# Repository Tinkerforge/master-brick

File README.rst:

Master Brick
============

This repository contains the firmware source code and the hardware design
files. The documentation generator configs can be found at
https://github.com/Tinkerforge/generators

Repository Content
------------------

software/:
 * examples/: Examples for all supported languages
 * build/: Compiled files
 * src/: Source code of firmware
 * Makefile: Makefile to build project

hardware/:
 * Contains KiCad project files and additionally schematics as PDF

datasheets/:
 * Contains datasheets for sensors and complex ICs that are used

Hardware
--------

The hardware is designed with the open source EDA Suite KiCad
(http://www.kicad.org). Before you are able to open the files,
you have to install the Tinkerforge kicad-libraries
(https://github.com/Tinkerforge/kicad-libraries). You can either clone
them directly in hardware/ or clone them in a separate folder and
symlink them into hardware/
(ln -s kicad_path/kicad-libraries project_path/hardware). After that you
can open the .pro file in hardware/ with KiCad and from there view and
modify the schematics and the PCB layout.

Software
--------

If you want to do your own Brick/Bricklet firmware development we highly
recommend that you use our build environment setup script and read the
tutorial (https://www.tinkerforge.com/en/doc/Tutorials/Tutorial_Build_Environment/Tutorial.html).

To compile the C code we recommend you to install the newest GNU Arm Embedded
Toolchain (https://launchpad.net/gcc-arm-embedded/+download).
You also need to install bricklib (https://github.com/Tinkerforge/bricklib).

You can either clone it directly in software/src/ or clone it in a
separate folder and symlink it into software/src/
(ln -s bricklib_path/bricklib project_path/software/src/). Finally make sure to
have CMake installed (http://www.cmake.org/cmake/resources/software.html).

After that you can build the firmware by invoking make in software/.
The firmware (.bin) can then be found in software/build/ and uploaded
with brickv (click button "Flashing" on start screen).

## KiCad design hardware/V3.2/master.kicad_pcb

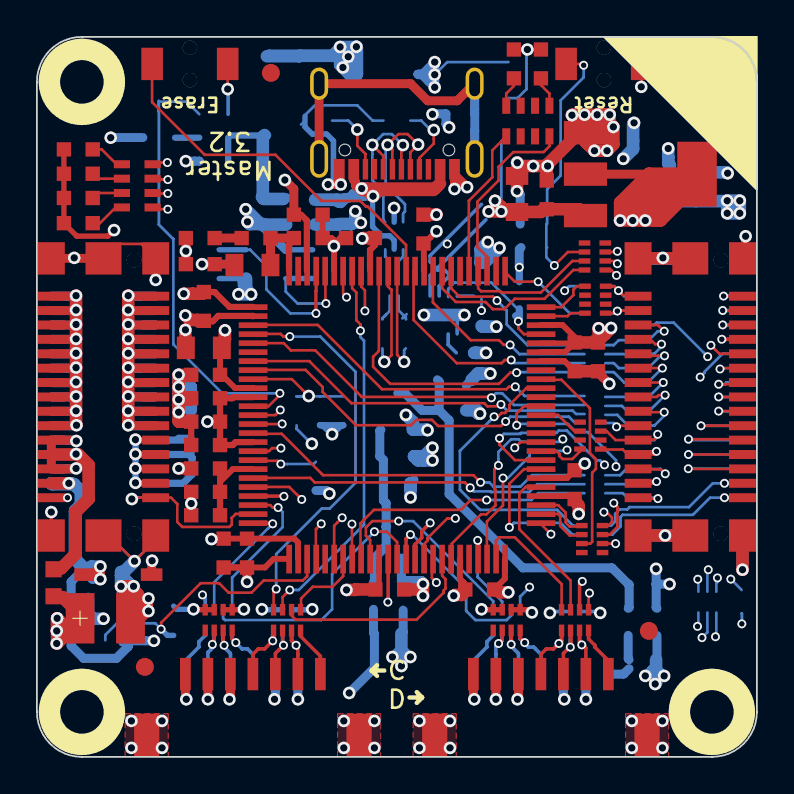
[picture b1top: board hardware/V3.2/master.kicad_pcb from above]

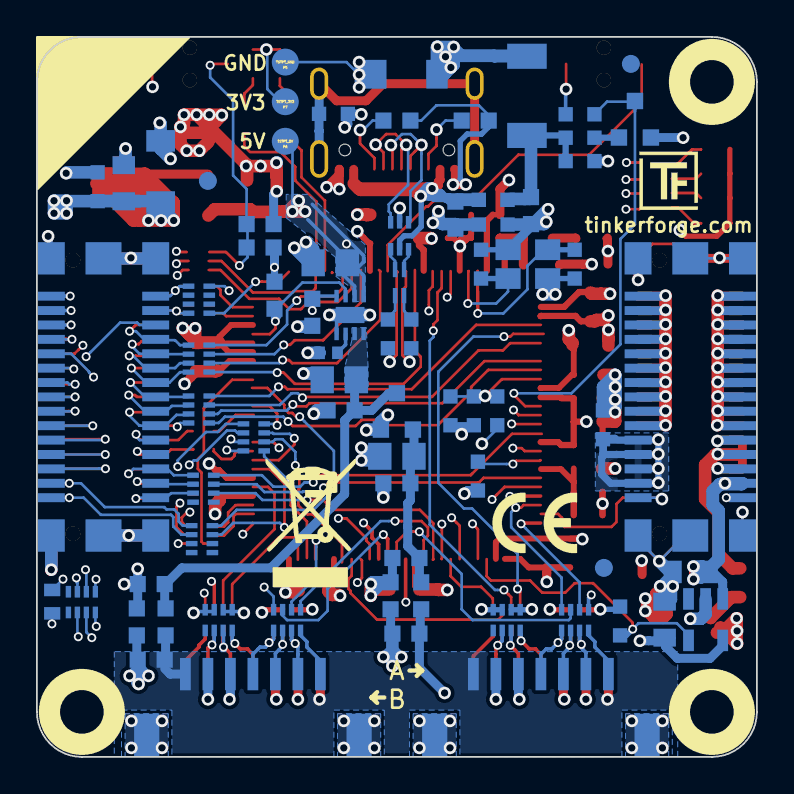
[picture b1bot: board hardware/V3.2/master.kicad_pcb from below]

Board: 4 copper layers, 40.0 x 40.0 mm, 137 parts (76 on the bottom side), 151 nets.

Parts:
C10, C11, C12, C13: DNP; C0603
C14, C46, C47: 1uF; C0603F
C15, C21, C29, C35, C39: 10µF/10V; C0805
C16, C20, C22, C23, C24, C25, C26, C28, C30, C31, C32, C33, C34, C37, C38, C401: 100nF; C0603
C17: 100µF; 3528-21
C18, C19, C36: 4.7µF; C0603
C27: 2.2µF; C0603
C40: DNP; C0402F
C41, C43, C45: 10uF; C0805E
C42, C44: 100nF; C0603F
C48, C49, C50, C51: 2.2uF; C0603F
C101: 4.7nF; C0603F
CP1, CP2, CP3, CP4: 220pF; 4X0402
D1, D3, D4, D5, D6: blue; D0603
D2: red; D0603
D11: PMEG4050; SOD-128
D12: Z5V; MiniMelf
D13: Z3.3V; MiniMelf
D14: B0520LW; SOD-123
FB1, FB3, FB101, FB102: FB; C0603
FB4: FB; R0603F
Fiducial_Mark: VAL**; Fiducial_Mark
Fiducial_Mark#2, Fiducial_Mark#3, Fiducial_Mark#4, Fiducial_Mark#5, Fiducial_Mark#6: VAL**; Fiducial_Mark
J1: USB-C; USB-C-2
J2, J3, J4, J5: DRILL; DRILL_NP
J6: STACK-UP-HIGH; BTB08-ACS-TOP
J7: STACK-HIGH; BTB08-ACS-BTM
J8: STACK-UP-LOW; BTB08-ACS-TOP
J9: STACK-DOWN; BTB08-ACS-BTM
L1: 744230900; WE-CNSW-0603
L2: LBR2012T100K; C0805
L3, L4, L5, L6: FB; R0603F
P1: Port A; CON-SENSOR2
P2: Port B; CON-SENSOR2
P3: Port C; CON-SENSOR2
P4: Port D; CON-SENSOR2
P5: TSTPT_GND; TSTPT
P6: TSTPT_5V; TSTPT
P7: TSTPT_3V3; TSTPT
Q1: 2N7002P; SOT23GDS
R3, R4: 27; R0603
R5, R18: 5k1; R0603F
R6: 47k; R0603
R7: 1k; R0603F
R8, R11, R17: 10k; R0603
R9, R10, R12, R13: DNP; R0603
R15: 100k; R0603
R16: 1R0; R0603
R101: 100k; R0603F
R301: 82; R0402E
RP3, RP4: 1k; 0603X4
RP5, RP6, RP7, RP9, RP301, RP302, RP303, RP304, RP305, RP306, RP307, RP308, RP310: 82; 4X0402
RP8, RP309: 1k; 4X0402
SW1: Reset; TACT-SWITCH
SW2: Erase; TACT-SWITCH
U1: SAM4S4CA; LQFP100
U2: 82400152; SOT563-SPEC
U3: TPS22975; WSON8-2x2
U4: AP7333-33SRG; SOT23-3
U12: LD1117; SOT-223
U13: STMPS2171STR; SOT23-5L
VAL: WEEE_7mm
VAL#2: CE_5mm
X1: 16Mhz; CRYSTAL_3225

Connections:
3,3VBricklet: C51.2, L4.1, P1.3, P2.3, P3.3, P4.3
3V3: C15.1, C16.1, C18.1, C19.1, C20.1, C22.1, C24.1, C25.1, C26.1, C29.1, C31.1, C35.1, C38.1, D1.1 (A), D2.1 (A), D3.1 (A), D4.1 (A), D5.1 (A), D6.1 (A), D13.2 (K), D14.1 (A), P7.1, R7.1, R9.2, R11.1, R12.2, R101.2, SW2.2, U1.1 (ADVREF), U1.10 (VDDIN), U1.27 (VDDIO), U1.50 (VDDIO), U1.69 (VDDIO), U1.91 (VDDIO), U1.98 (VDDIO), U12.2 (VOUT), U13.5 (IN)
3V3-EN: R17.1, U1.28 (PA16/PGMD4), U13.4 (EN)
5VBricklet: C48.2, L3.2, P1.1, P2.1, P3.1, P4.1
Bricklet_Enable: R7.2, U1.72 (PA1/PGMEN1), U3.3 (ON)
GND: C10.2, C11.2, C12.2, C13.2, C14.2, C15.2, C16.2, C17.2, C18.2, C19.2, C20.2, C21.2, C22.2, C23.2, C24.2, C25.2, C26.2, C27.2, C28.2, C29.2, C30.2, C31.2, C32.2, C33.2, C34.2, C35.2, C36.2, C37.2, C38.2, C39.2, C40.2, C41.1, C42.1, C43.1, C44.1, C45.1, C46.1, C49.1, C50.1, C101.1, C401.2, CP1.5 (R4), CP1.6 (R3), CP1.7 (R2), CP1.8 (R1), CP2.5 (R4), CP2.6 (R3), CP2.7 (R2), CP2.8 (R1), CP3.5 (R4), CP3.6 (R3), CP3.7 (R2), CP3.8 (R1), CP4.5 (R4), CP4.6 (R3), CP4.7 (R2), CP4.8 (R1), D12.1 (A), D13.1 (A), FB3.2, FB101.1, FB102.2, J6.EP, J7.EP, J8.EP, J9.EP, L5.1, L6.2, P5.1, Q1.S, R6.1, R10.1, R13.1, R15.1, R17.2, SW1.2, U1.2 (GND), U1.22 (PA23), U1.26 (GND), U1.45 (GND), U1.54 (PC28), U1.70 (GND), U1.71 (PC14), U1.73 (PC16), U1.95 (GND), U3.5 (GND), U3.EXP, U4.1 (GND), U12.1 (GND), U13.2 (GND), X1.3
GNDD1: C48.1, C51.1, L5.2, L6.1, P1.2, P1.EP, P2.2, P2.EP, P3.2, P3.EP, P4.2, P4.EP
LED1: RP4.1, U1.92 (PC24)
LED2: RP4.2, U1.94 (PC25)
LED3: RP4.3, U1.13 (PC26)
LED4: RP4.4, U1.17 (PC27)
unnamed: C10.1, R9.1, R10.2, U1.9 (PB3/AD7)
unnamed: C11.1, R12.1, R13.2, U1.19 (PC15/AD11)
unnamed: C27.1, C28.1, C30.1, C32.1, C33.1, C34.1, C401.1, L2.1, U1.11 (VDDOUT), U1.16 (VDDCORE), U1.36 (VDDCORE), U1.56 (VDDCORE), U1.85 (VDDCORE)
unnamed: C36.1, R16.1
unnamed: C37.1, L2.2, R16.2, U1.100 (VDDPLL)
unnamed: C40.1, U3.6 (CT)
unnamed: C41.2, C42.2, C49.2, L3.1, U3.7 (VOUT), U3.8 (VOUT), U4.3 (VIN)
unnamed: C43.2, C44.2, C50.2, L4.2, U4.2 (VOUT)
unnamed: C47.2, FB1.2, J1.1 (5V), U2.5 (VDD)
unnamed: CP1.2, P1.6, RP5.7 (R2)
unnamed: CP1.3, P1.5, RP5.6 (R3)
unnamed: CP1.4, P1.4, RP5.5 (R4)
unnamed: CP2.2, P2.6, RP6.7 (R2)
unnamed: CP2.3, P2.5, RP6.6 (R3)
unnamed: CP2.4, P2.4, RP6.5 (R4)
unnamed: CP3.2, P3.6, RP7.7 (R2)
unnamed: CP3.3, P3.5, RP7.6 (R3)
unnamed: CP3.4, P3.4, RP7.5 (R4)
unnamed: CP4.2, P4.6, RP9.7 (R2)
unnamed: CP4.3, P4.5, RP9.6 (R3)
unnamed: CP4.4, P4.4, RP9.5 (R4)
unnamed: D1.2 (K), RP3.1
unnamed: D2.2 (K), RP3.4
unnamed: D3.2 (K), RP4.8 (R1)
unnamed: D4.2 (K), RP4.7 (R2)
unnamed: D5.2 (K), RP4.6 (R3)
unnamed: D6.2 (K), RP4.5 (R4)
unnamed: FB4.1, J8.22 (5V), J8.24 (5V), J8.26 (5V), J9.22 (5V), J9.24 (5V), J9.26 (5V)
unnamed: FB102.1, J1.SHD
unnamed: J1.2 (D-), U2.3 (IO2)
unnamed: J1.3 (D+), U2.1 (IO1)
unnamed: J1.4 (CC1), R5.1
unnamed: J1.5 (CC2), R18.1
unnamed: J6.1 (SPI-MISO), J7.1 (SPI-MISO), RP305.7 (R2)
unnamed: J6.2 (I2C-SDA/TDI), J7.2 (I2C-SDA/TDI), RP8.4, RP310.1
unnamed: J6.3 (SPI-MOSI), J7.3 (SPI-MOSI), RP305.6 (R3)
unnamed: J6.4 (I2C-SCL/TDO), J7.4 (I2C-SCL/TDO), RP8.1, RP310.4
unnamed: J6.5 (SPI-SCLK), J7.5 (SPI-SCLK), RP305.5 (R4)
unnamed: J6.6 (SEL-00), J7.8 (SEL-01), RP301.1
unnamed: J6.7 (RESET), J7.7 (RESET), RP309.7 (R2)
unnamed: J6.8 (SEL-01), J7.10 (SEL-02), RP301.2
unnamed: J6.9 (DETECT/TMS), RP309.6 (R3)
unnamed: J6.10 (SEL-02), J7.12 (SEL-03), RP301.3
unnamed: J6.11 (SYNC/GP/TCK), J7.11 (SYNC/GP/TCK), RP309.5 (R4)
unnamed: J6.12 (SEL-03), J7.14 (SEL-04), RP301.4
unnamed: J6.13 (EX-SPI-MISO), J7.13 (EX-SPI-MISO), RP306.8 (R1)
unnamed: J6.14 (SEL-04), J7.16 (SEL-05), RP302.1
unnamed: J6.15 (EX-SPI-MOSI), J7.15 (EX-SPI-MOSI), RP306.7 (R2)
unnamed: J6.16 (SEL-05), J7.18 (SEL-06), RP302.2
unnamed: J6.17 (EX-SPI-SCLK), J7.17 (EX-SPI-SCLK), RP306.6 (R3)
unnamed: J6.18 (SEL-06), J7.20 (SEL-07), RP302.3
unnamed: J6.19 (EX-0-GP00/nINT0), J7.19 (EX-0_GP00/nINT0), RP307.7 (R2)
unnamed: J6.20 (SEL-07), RP302.4
unnamed: J6.21 (EX-0-GP01/nINT1), J7.21 (EX-0_GP01/nINT1), RP307.8 (R1)
unnamed: J6.22 (EX-SEL-00), J7.22 (EX-SEL/EX-SEL-00), RP303.7 (R2)
unnamed: J6.23 (EX-0-GP02/nINT2), J7.23 (EX-0_GP02/nINT2), RP307.6 (R3)
unnamed: J6.24 (EX-SEL-01), J7.24 (EX-SEL-01), RP303.5 (R4)
unnamed: J6.25 (EX-1-GP00), J7.25 (EX-1_GP00), RP307.5 (R4)
unnamed: J6.26 (EX-SER2-RXD), J7.26 (EX-SER2-RXD), RP304.5 (R4)
unnamed: J6.27 (EX-1-GP01), J7.27 (EX-1_GP01), RP308.1
unnamed: J6.28 (EX-SER2-TXD), J7.28 (EX-SER2-TXD), RP304.6 (R3)
unnamed: J6.29 (EX-1-GP02), J7.29 (EX-1_GP02), RP308.2
unnamed: J6.30 (EX-SER2-RTS), J7.30 (EX-SER2-RTS), RP304.7 (R2)
unnamed: J7.6 (SEL/SEL-00), R301.2
unnamed: J8.1 (STACK-PGND), J8.3 (STACK-PGND), J8.5 (STACK-PGND), J8.7 (STACK-PGND), J8.9 (STACK-PGND), J8.11 (STACK-PGND), J8.13 (STACK-PGND), J8.15 (STACK-PGND), J8.17 (STACK-PGND), J8.19 (STACK-PGND), J9.1 (STACK-PGND), J9.3 (STACK-PGND), J9.5 (STACK-PGND), J9.7 (STACK-PGND), J9.9 (STACK-PGND), J9.11 (STACK-PGND), J9.13 (STACK-PGND), J9.15 (STACK-PGND), J9.17 (STACK-PGND), J9.19 (STACK-PGND)
unnamed: J8.2 (STACK-PVCC), J8.4 (STACK-PVCC), J8.6 (STACK-PVCC), J8.8 (STACK-PVCC), J8.10 (STACK-PVCC), J8.12 (STACK-PVCC), J8.14 (STACK-PVCC), J8.16 (STACK-PVCC), J8.18 (STACK-PVCC), J8.20 (STACK-PVCC), J9.2 (STACK-PVCC), J9.4 (STACK-PVCC), J9.6 (STACK-PVCC), J9.8 (STACK-PVCC), J9.10 (STACK-PVCC), J9.12 (STACK-PVCC), J9.14 (STACK-PVCC), J9.16 (STACK-PVCC), J9.18 (STACK-PVCC), J9.20 (STACK-PVCC)
unnamed: L1.1, U2.6 (IO1)
unnamed: L1.2, R4.1
unnamed: L1.3, R3.1
unnamed: L1.4, U2.4 (IO2)
unnamed: P1.7, RP5.8 (R1)
unnamed: P2.7, RP6.8 (R1)
unnamed: P3.7, RP7.8 (R1)
unnamed: P4.7, RP9.8 (R1)
unnamed: Q1.G, R8.2
unnamed: R3.2, U1.88 (PB10/DDM)
unnamed: R4.2, U1.89 (PB11/DDP)
unnamed: RP3.5 (R4), U1.80 (PC19)
unnamed: RP3.8 (R1), U1.78 (PC18)
unnamed: SW2.1, U1.87 (PB12/ERASE)
PGND: FB3.1, J8.21 (GND), J8.23 (GND), J8.25 (GND), J8.27 (GND), J9.21 (GND), J9.23 (GND), J9.25 (GND), J9.27 (GND)
Port-A-CLK: RP5.3, U1.38 (PA25)
Port-A-CS: RP5.4, U1.23 (PC12/AD12)
Port-A-MISO: RP5.1, U1.37 (PC4)
Port-A-MOSI: RP5.2, U1.25 (PC0)
Port-B-CLK: RP6.3, U1.39 (PA26)
Port-B-CS: RP6.4, U1.21 (PC13/AD10)
Port-B-MISO: RP6.1, U1.35 (PC5)
Port-B-MOSI: RP6.2, U1.47 (PC1)
Port-C-CLK: RP7.3, U1.93 (PB13/DAC0)
Port-C-CS: RP7.4, U1.4 (PC29/AD13)
Port-C-MISO: RP7.1, U1.32 (PC6)
Port-C-MOSI: RP7.2, U1.43 (PC2)
Port-D-CLK: RP9.3, U1.55 (PA4/PGMNCMD)
Port-D-CS: RP9.4, U1.49 (PA7/XIN32/PGMNVALID)
Port-D-MISO: RP9.1, U1.29 (PC7)
Port-D-MOSI: RP9.2, U1.40 (PC3)
SCL-PULLUP: RP8.5 (R4), U1.75 (PC17)
SDA-PULLUP: RP8.8 (R1), U1.74 (PA0/PGMEN0)
STACK-CURRENT: J8.29 (CURRENT), J9.29 (CURRENT), U1.24 (PA20/AD3)
STACK-EX-0-GP00: RP307.2, U1.44 (PA10/PGMM2)
STACK-EX-0-GP01: RP307.1, U1.48 (PA8/XOUT32/PGMM0)
STACK-EX-0-GP02: RP307.3, U1.58 (PC8)
STACK-EX-1-GP00: RP307.4, U1.64 (PA30)
STACK-EX-1-GP01: RP308.8 (R1), U1.66 (PA3)
STACK-EX-1-GP02: RP308.7 (R2), U1.57 (PA27)
STACK-HIGH/JTAG-TMS: RP309.3, U1.79 (PB6/TMS)
STACK-I2C-SCL/JTAG-TDO: RP310.5 (R4), U1.76 (PB5/TDO)
STACK-I2C-SDA/JTAG-TDI: RP310.8 (R1), U1.51 (PB4/TDI)
STACK-MASTER-DETECT: J7.9 (DETECT/TMS), U1.14 (PA18/PGMD6/AD1)
STACK-RESET: C101.2, R101.1, RP309.2, SW1.1, U1.60 (NRST)
STACK-SELECT-00: RP301.8 (R1), U1.82 (PC20)
STACK-SELECT-01: RP301.7 (R2), U1.84 (PC21)
STACK-SELECT-02: RP301.6 (R3), U1.86 (PC22)
STACK-SELECT-03: RP301.5 (R4), U1.90 (PC23)
STACK-SELECT-04: RP302.8 (R1), U1.3 (PB0/AD4)
STACK-SELECT-05: RP302.7 (R2), U1.5 (PB1/AD5)
STACK-SELECT-06: RP302.6 (R3), U1.7 (PB2/AD6)
STACK-SELECT-07: RP302.5 (R4), U1.8 (PC31)
STACK-SELECT-EX-00: RP303.2, U1.63 (PA29)
STACK-SELECT-EX-01: RP303.4, U1.59 (PA28)
STACK-SER2-RTS: RP304.2, U1.34 (PA24)
STACK-SER2-RXD: RP304.4, U1.15 (PA21/AD8)
STACK-SER2-TXD: RP304.3, U1.20 (PA22/AD9)
STACK-SER-RXD: RP306.1, U1.53 (PA5/PGMRDY)
STACK-SER-SCK: RP306.3, U1.67 (PA2/PGMEN2)
STACK-SER-TXD: RP306.2, U1.52 (PA6/PGMNOE)
STACK-SPI-MISO: RP305.2, U1.41 (PA12/PGMD0)
STACK-SPI-MOSI: RP305.3, U1.33 (PA13/PGMD1)
STACK-SPI-SCLK: RP305.4, U1.31 (PA14/PGMD2)
STACK-SPI-SELECT: R301.1, U1.42 (PA11/PGMM3)
STACK-SYNC/JTAG-TCK: RP309.4, U1.83 (PB7/TCK)
STACK-VOLTAGE: J8.30 (VOLTAGE), J9.30 (VOLTAGE), R15.2, U1.18 (PA19/PGMD7/AD2)
USB-DETECT: Q1.D, R11.2, U1.12 (PA17/PGMD5/AD0)
USB_GND: C47.1, FB101.2, J1.6 (GND), R5.2, R18.2, U2.2 (GND)
VCC: C39.1, D14.2 (K), J8.28 (3V3), J9.28 (3V3), U13.1 (OUT)
VSTACK: C14.1, C17.1, C21.1, C23.1, C45.2, D11.2 (K), D12.2 (K), FB4.2, P6.1, U3.1 (VIN), U3.2 (VIN), U3.4 (VBIAS), U12.3 (VIN)
VUSB: C46.2, D11.1 (A), FB1.1, R6.2, R8.1
XIN: C13.1, U1.97 (PB9/PGMCK/XIN), X1.2
XOUT: C12.1, U1.96 (PB8/XOUT), X1.1

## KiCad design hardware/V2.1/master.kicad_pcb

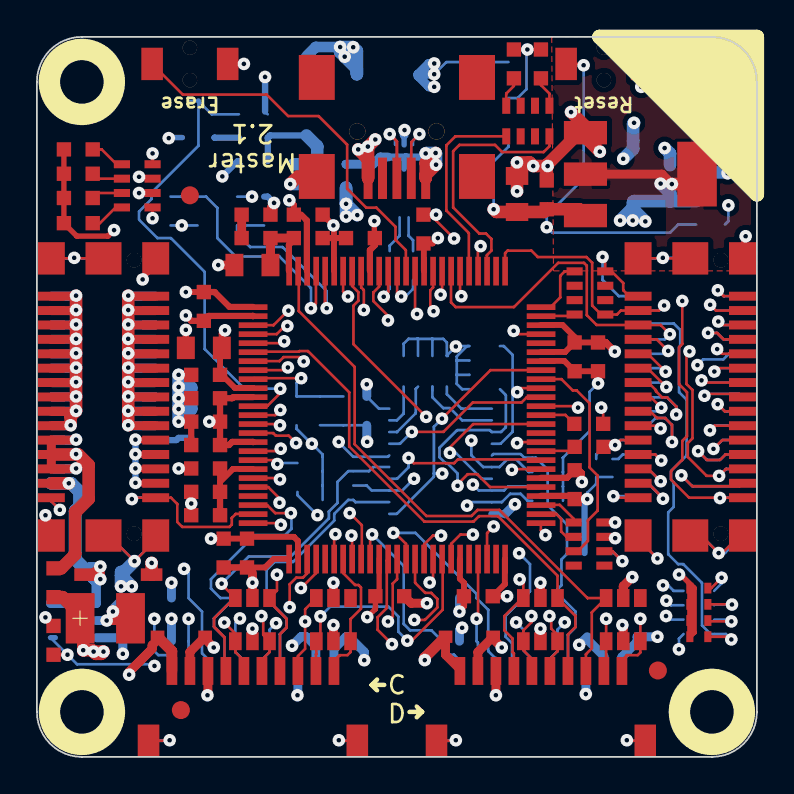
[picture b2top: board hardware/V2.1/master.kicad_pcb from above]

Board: 4 copper layers, 40.0 x 40.0 mm, 124 parts (0 on the bottom side), 122 nets.

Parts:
C1, C2, C3, C4, C5, C6, C7, C8, C9: DNP; C0402
C10, C11, C16, C20, C22, C23, C24, C25, C26, C28, C30, C31, C32, C33, C34, C37, C38: 100nF; C0603
C12, C13: DNP; C0603
C14: 1µF; C0603
C15, C21, C29, C35, C39: 10µF/10V; C0805
C17: 100µF; 3528-21
C18, C19, C36: 4.7µF; C0603
C27: 2.2µF; C0603
D1, D3, D4, D5, D6: blue; D0603
D2: red; D0603
D7, D8, D9, D10: ESD5V0D3B-TP; SOD-323
D11: PMEG4050; SOD-128
D12: Z5V; MiniMelf
D13: Z3.3V; MiniMelf
D14: B0520LW; SOD-123
FB1, FB2, FB3, FB4: FB; C0603
Fiducial_Mark: VAL**; Fiducial_Mark
Fiducial_Mark#2, Fiducial_Mark#3, Fiducial_Mark#4, Fiducial_Mark#5, Fiducial_Mark#6: VAL**; Fiducial_Mark
J1: USB-MINI-B-SMD
J2, J3, J4, J5: DRILL; DRILL_NP
J6, J8: STACK-UP-LOW; BTB08-ACS-TOP
J7, J9: STACK-DOWN; BTB08-ACS-BTM
L1: 744230900; WE-CNSW-0603
L2: LBR2012T100K; C0805
P1, P2, P3, P4: CON-SENSOR
P5: TSTPT_GND; TSTPT
P6: TSTPT_5V; TSTPT
P7: TSTPT_3V3; TSTPT
Q1: 2N7002P; SOT23EBC
R1, R2: 100; R0603
R3, R4: 27; R0603
R6: 47k; R0603
R8, R9, R11, R13, R17: 10k; R0603
R10, R12, R14: 1k; R0603
R15: 100k; R0603
R16: 1R0; R0603
RP1, RP2: 100; 0603X4
RP3, RP4, RP8: 1k; 0603X4
RP5, RP6, RP7: 2k2; 0603X4
RP9: 10k; 0603X4
SW1: Reset; TACT-SWITCH
SW2: Erase; TACT-SWITCH
U1: AT91SAM3SXC; LQFP100
U2: 82400152; SOT563-SPEC
U3: PCA9518PW; TSSOP20
U4, U5, U6, U7, U8, U9, U10, U11: CM1293A; SC-74
U12: LD1117; SOT-223
U13: RT9701XB; SOT23-5
VAL: CE_5mm
VAL#2: WEEE_7mm
X1: 16Mhz; CRYSTAL_3225

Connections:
3V3: C14.2, C15.1, C16.1, C18.1, C19.1, C20.1, C22.1, C24.1, C25.1, C26.1, C29.1, C31.1, C35.1, C38.1, D1.1, D2.1, D3.1, D4.1, D5.1, D6.1, D13.2, D14.1, P1.3, P2.3, P3.3, P4.3, P7.1, R9.2, R11.1, R12.2, RP5.1, RP5.2, RP5.3, RP5.4, RP6.1, RP6.2, RP6.3, RP6.4, RP7.1, RP7.2, RP7.3, RP7.4, RP9.1, RP9.2, RP9.3, RP9.4, SW2.2, U1.1, U1.10, U1.27, U1.50, U1.69, U1.91, U1.98, U3.20, U4.5, U5.5, U6.5, U7.5, U8.5, U9.5, U10.5, U11.5, U12.2, U13.3
3V3-EN: R17.1, U1.28, U13.4
BRICKLET-I2C-SCL: RP5.8, U1.55, U3.3
BRICKLET-I2C-SDA: RP5.5, U1.66, U3.4
BRICKLET-IO0_0/AD0: P1.7, U1.23, U4.1
BRICKLET-IO0_1: P1.8, U1.38, U8.3
BRICKLET-IO0_2/PWM0: P1.9, U1.25, U8.4
BRICKLET-IO0_3: P1.10, U1.37, U8.6
BRICKLET-IO1_0/AD1: P2.7, U1.21, U5.1
BRICKLET-IO1_1: P2.8, U1.39, U9.3
BRICKLET-IO1_2/PWM1: P2.9, U1.47, U9.4
BRICKLET-IO1_3: P2.10, U1.35, U9.6
BRICKLET-IO2_0/AD2: P3.7, U1.4, U6.1
BRICKLET-IO2_1/DA0: P3.8, U1.93, U10.3
BRICKLET-IO2_2/PWM2: P3.9, U1.43, U10.4
BRICKLET-IO2_3: P3.10, U1.32, U10.6
BRICKLET-IO3_0/AD3: P4.7, U1.6, U7.1
BRICKLET-IO3_1/DA1: P4.8, U1.99, U11.3
BRICKLET-IO3_2/PWM3: P4.9, U1.40, U11.4
BRICKLET-IO3_3: P4.10, U1.29, U11.6
BRICKLET-SEL-0: P1.6, U1.58, U3.14, U4.6
BRICKLET-SEL-1: P2.6, U1.62, U3.7, U5.6
BRICKLET-SEL-2: P3.6, U1.65, U3.17, U6.6
BRICKLET-SEL-3: P4.6, U1.68, U3.11, U7.6
GND: C1.2, C2.2, C3.2, C4.2, C5.2, C6.2, C7.2, C8.2, C9.2, C10.2, C11.2, C12.2, C13.2, C14.1, C15.2, C16.2, C17.2, C18.2, C19.2, C20.2, C21.2, C22.2, C23.2, C24.2, C25.2, C26.2, C27.2, C28.2, C29.2, C30.2, C31.2, C32.2, C33.2, C34.2, C35.2, C36.2, C37.2, C38.2, C39.2, D7.1, D8.1, D9.1, D10.1, D12.1, D13.1, FB2.1, FB3.2, J1.5, J6.EP, J7.EP, J8.EP, J9.EP, P1.2, P1.EP, P2.2, P2.EP, P3.2, P3.EP, P4.2, P4.EP, P5.1, Q1.1, R6.1, R10.1, R13.1, R15.1, R17.2, SW1.2, U1.2, U1.26, U1.45, U1.54, U1.70, U1.73, U1.95, U2.2, U3.10, U4.2, U5.2, U6.2, U7.2, U8.2, U9.2, U10.2, U11.2, U12.1, U13.2, X1.3
LED1: RP4.1, U1.92
LED2: RP4.2, U1.94
LED3: RP4.3, U1.13
LED4: RP4.4, U1.17
unnamed: C10.1, R9.1, R10.2, U1.9
unnamed: C11.1, R12.1, R13.2, U1.19
unnamed: C27.1, C28.1, C30.1, C32.1, C33.1, C34.1, L2.1, U1.11, U1.16, U1.36, U1.56, U1.85
unnamed: C36.1, R16.1
unnamed: C37.1, L2.2, R16.2, U1.100
unnamed: D1.2, RP3.1
unnamed: D2.2, RP3.4
unnamed: D3.2, RP4.8
unnamed: D4.2, RP4.7
unnamed: D5.2, RP4.6
unnamed: D6.2, RP4.5
unnamed: FB1.2, J1.1, U2.5
unnamed: FB2.2, J1.6
unnamed: FB3.1, J8.21, J8.23, J8.25, J8.27, J9.21, J9.23, J9.25, J9.27
unnamed: FB4.2, J8.22, J8.24, J8.26, J9.22, J9.24, J9.26
unnamed: J1.2, U2.3
unnamed: J1.3, U2.1
unnamed: J6.7, J7.7, R14.1
unnamed: J8.1, J8.3, J8.5, J8.7, J8.9, J8.11, J8.13, J8.15, J8.17, J8.19, J9.1, J9.3, J9.5, J9.7, J9.9, J9.11, J9.13, J9.15, J9.17, J9.19
unnamed: J8.2, J8.4, J8.6, J8.8, J8.10, J8.12, J8.14, J8.16, J8.18, J8.20, J9.2, J9.4, J9.6, J9.8, J9.10, J9.12, J9.14, J9.16, J9.18, J9.20
unnamed: L1.1, U2.6
unnamed: L1.2, R4.1
unnamed: L1.3, R3.1
unnamed: L1.4, U2.4
unnamed: P1.4, RP6.8, U3.12, U4.3
unnamed: P1.5, RP6.7, U3.13, U4.4
unnamed: P2.4, RP7.8, U3.5, U5.3
unnamed: P2.5, RP7.7, U3.6, U5.4
unnamed: P3.4, RP6.6, U3.15, U6.3
unnamed: P3.5, RP6.5, U3.16, U6.4
unnamed: P4.4, RP7.6, U3.8, U7.3
unnamed: P4.5, RP7.5, U3.9, U7.4
unnamed: Q1.2, R8.2
unnamed: R1.2, U1.59
unnamed: R2.2, U1.63
unnamed: R3.2, U1.88
unnamed: R4.2, U1.89
unnamed: RP1.1, U1.42
unnamed: RP1.2, U1.41
unnamed: RP1.3, U1.33
unnamed: RP1.4, U1.31
unnamed: RP2.1, U1.53
unnamed: RP2.2, U1.52
unnamed: RP2.3, U1.67
unnamed: RP3.5, U1.80
unnamed: RP3.8, U1.78
unnamed: RP9.5, U3.1
unnamed: RP9.6, U3.2
unnamed: RP9.7, U3.18
unnamed: RP9.8, U3.19
unnamed: SW2.1, U1.87
SCL-PULLUP: RP8.5, U1.75
SDA-PULLUP: RP8.8, U1.74
STACK-CURRENT: J8.29, J9.29, U1.24
STACK-EX-0-GP00: J6.19, J7.19, U1.48
STACK-EX-0-GP01: J6.21, J7.21, U1.44
STACK-EX-0-GP02: J6.23, J7.23, U1.57
STACK-EX-1-GP00: J6.25, J7.25, U1.72
STACK-EX-1-GP01: J6.27, J7.27, U1.64
STACK-EX-1-GP02: J6.29, J7.29, U1.81
STACK-HIGH/JTAG-TMS: J6.9, U1.79
STACK-I2C-SCL/JTAG-TDO: J6.4, J7.4, RP8.1, U1.76
STACK-I2C-SDA/JTAG-TDI: J6.2, J7.2, RP8.4, U1.51
STACK-MASTER-DETECT: J7.9, U1.14
STACK-RESET: R14.2, SW1.1, U1.60
STACK-SELECT-00: J6.6, J7.8, U1.82
STACK-SELECT-01: J6.8, J7.10, U1.84
STACK-SELECT-02: J6.10, J7.12, U1.86
STACK-SELECT-03: J6.12, J7.14, U1.90
STACK-SELECT-04: J6.14, J7.16, U1.3
STACK-SELECT-05: J6.16, J7.18, U1.5
STACK-SELECT-06: J6.18, J7.20, U1.7
STACK-SELECT-07: J6.20, U1.8
STACK-SELECT-EX-00: C1.1, J6.22, J7.22, R1.1
STACK-SELECT-EX-01: C2.1, J6.24, J7.24, R2.1
STACK-SER2-RTS: J6.30, J7.30, U1.34
STACK-SER2-RXD: J6.26, J7.26, U1.15
STACK-SER2-TXD: J6.28, J7.28, U1.20
STACK-SER-RXD: C8.1, J6.13, J7.13, RP2.8
STACK-SER-SCK: C4.1, J6.17, J7.17, RP2.6
STACK-SER-TXD: C6.1, J6.15, J7.15, RP2.7
STACK-SPI-MISO: C5.1, J6.1, J7.1, RP1.7
STACK-SPI-MOSI: C7.1, J6.3, J7.3, RP1.6
STACK-SPI-SCLK: C9.1, J6.5, J7.5, RP1.5
STACK-SPI-SELECT: C3.1, J7.6, RP1.8
STACK-SYNC/JTAG-TCK: J6.11, J7.11, U1.83
STACK-VOLTAGE: J8.30, J9.30, R15.2, U1.18
USB-DETECT: Q1.3, R11.2, U1.12
VPP: C39.1, D14.2, J8.28, J9.28, U13.1, U13.5
VSTACK: C17.1, C21.1, C23.1, D7.2, D8.2, D9.2, D10.2, D11.2, D12.2, FB4.1, P1.1, P2.1, P3.1, P4.1, P6.1, U12.3
VUSB: D11.1, FB1.1, R6.2, R8.1
XIN: C13.1, U1.97, X1.2
XOUT: C12.1, U1.96, X1.1

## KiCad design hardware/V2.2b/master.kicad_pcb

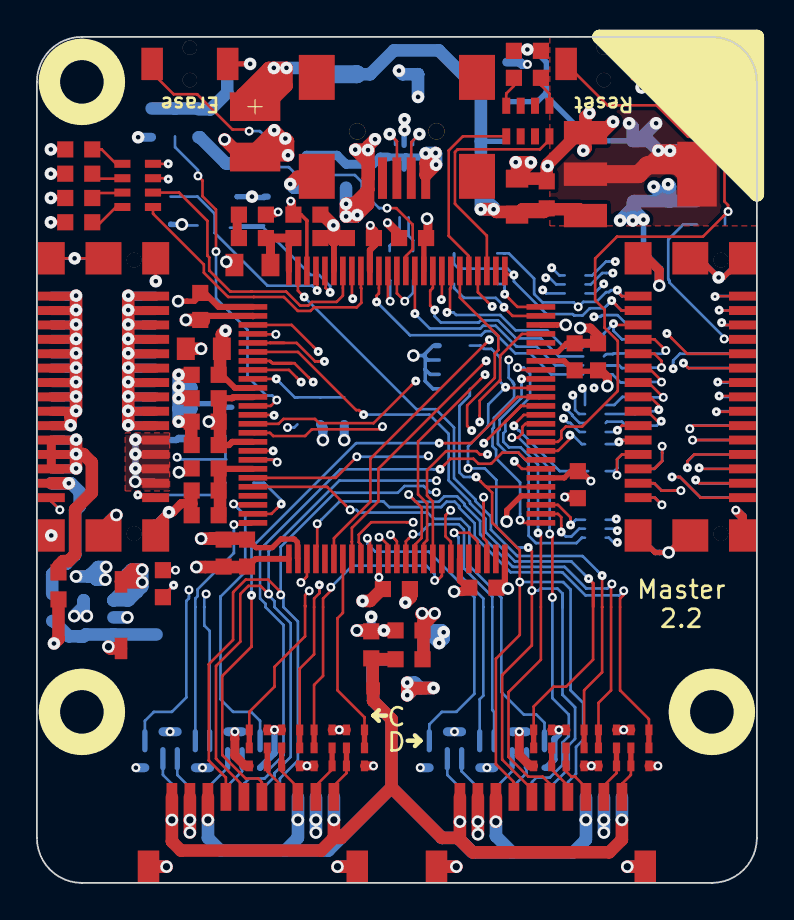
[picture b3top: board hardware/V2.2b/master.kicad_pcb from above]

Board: 4 copper layers, 40.0 x 47.0 mm, 149 parts (0 on the bottom side), 138 nets.

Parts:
C101, C102, C402, C406, C408, C409, C410, C411, C412, C414, C416, C417, C418, C419, C420, C423, C424: 100nF; C0603F
C103, C104: DNP; C0603F
C201, C202, C203, C204: 1µF; C0603F
C205, C206, C207, C208, C209, C210, C211, C212, C213, C214, C215, C216, C217, C218, C219, C220, C221, C222, C223, C224, C225, C226, C227, C228, C229, C230, C231, C232, C233, C234, C235, C236: C; 0402
C401, C407, C415, C421, C425: 10µF/10V; C0805
C403: 100µF; 3528-21
C404, C405, C422: 4.7µF; C0603F
C413: 2.2µF; C0603F
D101, D103, D104, D105, D106: blue; D0603F
D102: red; D0603F
D201: ESD5V0D3B-TP; SOD-323
D202: ESD3V3D3B-TP; SOD-323
D401: PMEG4050; SOD-128
D402: Z5V; MiniMelf
D403: Z3.3V; MiniMelf
D404: B0520LW; SOD-123
F101: PTC; 1206
FB101, FB102, FB302, FB303: FB; R0603F
FB201, FB202: FILTER; R0603F
FB301: 0; R0805
J101: USB-MINI-B-SMD
J102, J103, J104, J105: DRILL; DRILL_NP
J301, J303: STACK-UP-LOW; BTB08-ACS-TOP
J302, J304: STACK-DOWN; BTB08-ACS-BTM
L101: 744230900; WE-CNSW-0603
L401: LBR2012T100K; R0805
P201, P202, P203, P204: CON-SENSOR
P401: TSTPT_GND; TSTPT
P402: TSTPT_5V; TSTPT
P403: TSTPT_3V3; TSTPT
R101, R102: 27; R0603F
R103, R108, R402: 10k; R0603F
R104, R107, R301: 1k; R0603F
R105: 27k; R0603F
R106: 18k; R0603F
R201, R202, R203, R204, R205, R206, R207, R208, R209, R210, R211, R212, R213, R214, R215, R216: R; 0402
R302, R303: 10; R0603F
R304: 100k; R0603F
R401: 1R0; R0603F
RP101, RP102, RP301: 1k; 0603X4
RP201: 2k2; 0603X4
RP302, RP303, RP304, RP305, RP306: TBD; 4X0402
SW101: Reset; TACT-SWITCH
SW102: Erase; TACT-SWITCH
U101: AT91SAM3SXC; LQFP100
U102: 82400152; SOT563-SPEC
U401: LD1117; SOT-223
U402: RT9701XB; SOT23-5
X101: 16Mhz; CRYSTAL_3225

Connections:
3V3: C202.2, C401.1, C402.1, C404.1, C405.1, C406.1, C408.1, C410.1, C411.1, C412.1, C415.1, C417.1, C421.1, C424.1, D101.1, D102.1, D103.1, D104.1, D105.1, D106.1, D403.2, D404.1, FB202.1, P403.1, R103.2, R107.2, RP201.1, RP201.2, RP201.3, RP201.4, SW102.2, U101.1, U101.10, U101.27, U101.50, U101.54, U101.69, U101.91, U101.98, U401.2, U402.3
3V3-EN: R402.1, U101.28, U402.4
BRICKLET-I2C-SCL: P201.4, P202.4, P203.4, P204.4, RP201.8, U101.55
BRICKLET-I2C-SDA: P201.5, P202.5, P203.5, P204.5, RP201.5, U101.66
BRICKLET-IO0_0/AD0: C205.2, R201.2, U101.23
BRICKLET-IO0_1: C206.2, R202.2, U101.38
BRICKLET-IO0_2/PWM0: C207.2, R203.2, U101.25
BRICKLET-IO0_3: C208.2, R204.2, U101.37
BRICKLET-IO1_0/AD1: C213.2, R205.2, U101.21
BRICKLET-IO1_1: C216.2, R206.2, U101.39
BRICKLET-IO1_2/PWM1: C219.2, R207.2, U101.47
BRICKLET-IO1_3: C222.2, R208.2, U101.35
BRICKLET-IO2_0/AD2: C214.2, R209.2, U101.4
BRICKLET-IO2_1/DA0: C217.2, R210.2, U101.93
BRICKLET-IO2_2/PWM2: C220.2, R211.2, U101.43
BRICKLET-IO2_3: C223.2, R212.2, U101.32
BRICKLET-IO3_0/AD3: C215.2, R213.2, U101.6
BRICKLET-IO3_1/DA1: C218.2, R214.2, U101.99
BRICKLET-IO3_2/PWM3: C221.2, R215.2, U101.40
BRICKLET-IO3_3: C224.2, R216.2, U101.29
BRICKLET-SEL-0: P201.6, U101.58
BRICKLET-SEL-1: P202.6, U101.62
BRICKLET-SEL-2: P203.6, U101.65
BRICKLET-SEL-3: P204.6, U101.68
GND: C101.2, C102.2, C103.2, C104.2, C201.1, C202.1, C203.1, C204.1, C205.1, C206.1, C207.1, C208.1, C209.1, C210.1, C211.1, C212.1, C213.1, C214.1, C215.1, C216.1, C217.1, C218.1, C219.1, C220.1, C221.1, C222.1, C223.1, C224.1, C225.1, C226.1, C227.1, C228.1, C229.1, C230.1, C231.1, C232.1, C233.1, C234.1, C235.1, C236.1, C401.2, C402.2, C403.2, C404.2, C405.2, C406.2, C407.2, C408.2, C409.2, C410.2, C411.2, C412.2, C413.2, C414.2, C415.2, C416.2, C417.2, C418.2, C419.2, C420.2, C421.2, C422.2, C423.2, C424.2, C425.2, D201.1, D202.1, D402.1, D403.1, FB101.1, FB301.2, J101.5, J301.EP, J302.EP, J303.EP, J304.EP, P201.2, P201.EP, P202.2, P202.EP, P203.2, P203.EP, P204.2, P204.EP, P401.1, R104.1, R105.1, R108.1, R304.1, R402.2, SW101.2, U101.2, U101.26, U101.45, U101.70, U101.73, U101.95, U102.2, U401.1, U402.2, X101.3
LED1: RP102.1, U101.92
LED2: RP102.2, U101.94
LED3: RP102.3, U101.13
LED4: RP102.4, U101.17
unnamed: C101.1, R103.1, R104.2, U101.9
unnamed: C102.1, R107.1, R108.2, U101.19
unnamed: C203.2, D201.2, FB201.2, P201.1, P202.1, P203.1, P204.1
unnamed: C204.2, D202.2, FB202.2, P201.3, P202.3, P203.3, P204.3
unnamed: C209.2, P201.7, R201.1
unnamed: C210.2, P201.8, R202.1
unnamed: C211.2, P201.9, R203.1
unnamed: C212.2, P201.10, R204.1
unnamed: C225.2, P202.7, R205.1
unnamed: C226.2, P203.7, R209.1
unnamed: C227.2, P204.7, R213.1
unnamed: C228.2, P202.8, R206.1
unnamed: C229.2, P203.8, R210.1
unnamed: C230.2, P204.8, R214.1
unnamed: C231.2, P202.9, R207.1
unnamed: C232.2, P203.9, R211.1
unnamed: C233.2, P204.9, R215.1
unnamed: C234.2, P202.10, R208.1
unnamed: C235.2, P203.10, R212.1
unnamed: C236.2, P204.10, R216.1
unnamed: C413.1, C414.1, C416.1, C418.1, C419.1, C420.1, L401.1, U101.11, U101.16, U101.36, U101.56, U101.85
unnamed: C422.1, R401.1
unnamed: C423.1, L401.2, R401.2, U101.100
unnamed: D101.2, RP101.1
unnamed: D102.2, RP101.4
unnamed: D103.2, RP102.8
unnamed: D104.2, RP102.7
unnamed: D105.2, RP102.6
unnamed: D106.2, RP102.5
unnamed: F101.1, J101.1, U102.5
unnamed: F101.2, FB102.1
unnamed: FB101.2, J101.6
unnamed: FB301.1, J303.21, J303.23, J303.25, J303.27, J304.21, J304.23, J304.25, J304.27
unnamed: FB302.2, J303.22, J303.24, J303.26, J304.22, J304.24, J304.26
unnamed: FB303.1, J303.28, J304.28
unnamed: J101.2, U102.3
unnamed: J101.3, U102.1
unnamed: J301.1, J302.1, RP302.2
unnamed: J301.3, J302.3, RP302.3
unnamed: J301.5, J302.5, RP302.4
unnamed: J301.6, J302.8, RP303.1
unnamed: J301.7, J302.7, R301.1
unnamed: J301.8, J302.10, RP303.2
unnamed: J301.10, J302.12, RP303.3
unnamed: J301.12, J302.14, RP303.4
unnamed: J301.13, J302.13, RP305.2
unnamed: J301.14, J302.16, RP304.1
unnamed: J301.15, J302.15, RP305.3
unnamed: J301.16, J302.18, RP304.2
unnamed: J301.17, J302.17, RP305.4
unnamed: J301.18, J302.20, RP304.3
unnamed: J301.20, RP304.4
unnamed: J301.22, J302.22, RP306.1
unnamed: J301.24, J302.24, RP306.4
unnamed: J303.1, J303.3, J303.5, J303.7, J303.9, J303.11, J303.13, J303.15, J303.17, J303.19, J304.1, J304.3, J304.5, J304.7, J304.9, J304.11, J304.13, J304.15, J304.17, J304.19
unnamed: J303.2, J303.4, J303.6, J303.8, J303.10, J303.12, J303.14, J303.16, J303.18, J303.20, J304.2, J304.4, J304.6, J304.8, J304.10, J304.12, J304.14, J304.16, J304.18, J304.20
unnamed: J303.29, J304.29, R302.1
unnamed: J303.30, J304.30, R303.1, R304.2
unnamed: L101.1, U102.6
unnamed: L101.2, R102.1
unnamed: L101.3, R101.1
unnamed: L101.4, U102.4
unnamed: R101.2, U101.88
unnamed: R102.2, U101.89
unnamed: RP101.5, U101.80
unnamed: RP101.8, U101.78
unnamed: SW102.1, U101.87
SCL-PULLUP: RP301.4, U101.74
SDA-PULLUP: RP301.1, U101.75
STACK-CURRENT: R302.2, U101.24
STACK-EX-0-GP00: J301.19, J302.19, U101.48
STACK-EX-0-GP01: J301.21, J302.21, U101.44
STACK-EX-0-GP02: J301.23, J302.23, U101.57
STACK-EX-1-GP00: J301.25, J302.25, U101.72
STACK-EX-1-GP01: J301.27, J302.27, U101.64
STACK-EX-1-GP02: J301.29, J302.29, U101.81
STACK-HIGH/JTAG-TMS: J301.9, U101.79
STACK-I2C-SCL/JTAG-TDO: J301.4, J302.4, RP301.5, U101.76
STACK-I2C-SDA/JTAG-TDI: J301.2, J302.2, RP301.8, U101.51
STACK-MASTER-DETECT: J302.9, U101.14
STACK-RESET: R301.2, SW101.1, U101.60
STACK-SELECT-00: RP303.8, U101.82
STACK-SELECT-01: RP303.7, U101.84
STACK-SELECT-02: RP303.6, U101.86
STACK-SELECT-03: RP303.5, U101.90
STACK-SELECT-04: RP304.8, U101.3
STACK-SELECT-05: RP304.7, U101.5
STACK-SELECT-06: RP304.6, U101.7
STACK-SELECT-07: RP304.5, U101.8
STACK-SELECT-EX-00: RP306.8, U101.59
STACK-SELECT-EX-01: RP306.5, U101.63
STACK-SER2-RTS: J301.30, J302.30, U101.34
STACK-SER2-RXD: J301.26, J302.26, U101.15
STACK-SER2-TXD: J301.28, J302.28, U101.20
STACK-SER-RXD: RP305.7, U101.53
STACK-SER-SCK: RP305.5, U101.67
STACK-SER-TXD: RP305.6, U101.52
STACK-SPI-MISO: RP302.7, U101.41
STACK-SPI-MOSI: RP302.6, U101.33
STACK-SPI-SCLK: RP302.5, U101.31
STACK-SPI-SELECT: J302.6, U101.42
STACK-SYNC/JTAG-TCK: J301.11, J302.11, U101.83
STACK-VOLTAGE: R303.2, U101.18
USB-DETECT: R106.2, U101.12
VPP: C425.1, D404.2, FB303.2, U402.1, U402.5
VSTACK: C201.2, C403.1, C407.1, C409.1, D401.2, D402.2, FB201.1, FB302.1, P402.1, U401.3
VUSB: D401.1, FB102.2, R105.2, R106.1
XIN: C104.1, U101.97, X101.2
XOUT: C103.1, U101.96, X101.1

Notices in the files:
hardware/V2.1/master.kicad_pcb:
Licensed under CERN OHL v.1.1
Copyright (©) 2017, B.Nordmeyer
Copyright Tinkerforge GmbH 2017.
This documentation describes Open Hardware and is licensed under the
CERN OHL v. 1.1.
hardware/V2.2/master.kicad_pcb:
Copyright (©) 2011, B.Nordmeyer
Copyright Tinkerforge GmbH 2011.
hardware/V2.2b/master.kicad_pcb:
Copyright (©) 2017, L.Lauer
hardware/V3.2/master.kicad_pcb:
Copyright (©) 2022, B.Nordmeyer
Copyright Tinkerforge GmbH 2022.
